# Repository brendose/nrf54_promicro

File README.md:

<h1 align="center">Welcome to Project: nrf54_promicro </br> (nRF54L1x Pro Micro inspired development board) </h1>
<div align="center">

<a href="#introduction">Introduction</a> &nbsp;&bull;&nbsp;
<a href="#directory">Directory</a> &nbsp;&bull;&nbsp;
<a href="#documentation">Documentation</a> &nbsp;&bull;&nbsp;
<a href="#notes">Notes</a>
</div>

# Introduction
The <b>nrf54_promicro</b> project revolutionizes nRF52840 based keyboard projects by utilizing the Nordic Semiconductors nRF54L10/L15 Bluetooth transceiver, achieving sub-100uA/MHz power draw!
<br>
<br>
We're challenging the status quo of limited wireless keyboard battery life with the nRF54L15/L10, achieving unprecedented power efficiency. Why? Because Bluetooth based keyboard designs require decent battery life.
The nRF52840 power draw limits the battery life of most keyboard based projects, however, moving to the nRF54 the power draw can be minimized to a under 100uA/MHz. This Pro Micro-inspired board, designed in KiCad 9, 
integrates optimized power circuitry such as; the use of a high efficiency switching power supply, carefully selected low quiescent current (Iq) load switch and meticulous RF antenna tuning, wasting no power and
offering a development platform for keyboards that redefines what it means to have "good battery life".

The board contains:

- A Nordic Semiconductors nRF54L10 / nRF54L15 (ARM Cortex M33 and RISC-V coprocessor)
- 2.45GHz Chip Antenna supporting Bluetooth LE
- Texas Instruments BQ24075 battery charger
- 2x 13 pin GPIO headers 
- USB-C connector, with bit-banged USB interface
- Charge Status indicator LED
- Bluetooth Status indicator LED

### Projects top-level directory

    .
    ├── bom                      # Bill of Materials
    ├── images                   # Images used on this GitHub page
    ├── libs                     # Local component library
    ├── plots                    # Assembly drawings of the design
    ├── schematics               # Schematics of the design      
    └── README.md

## Documentation

TBD

## Notes

This repository is not actively maintained, so if you spot any bugs, please <a href="hhttps://github.com/brendose/nrf54_promicro/issues/new">raise an issue</a> and I will try get to it.

This is not an officially supported Google product.

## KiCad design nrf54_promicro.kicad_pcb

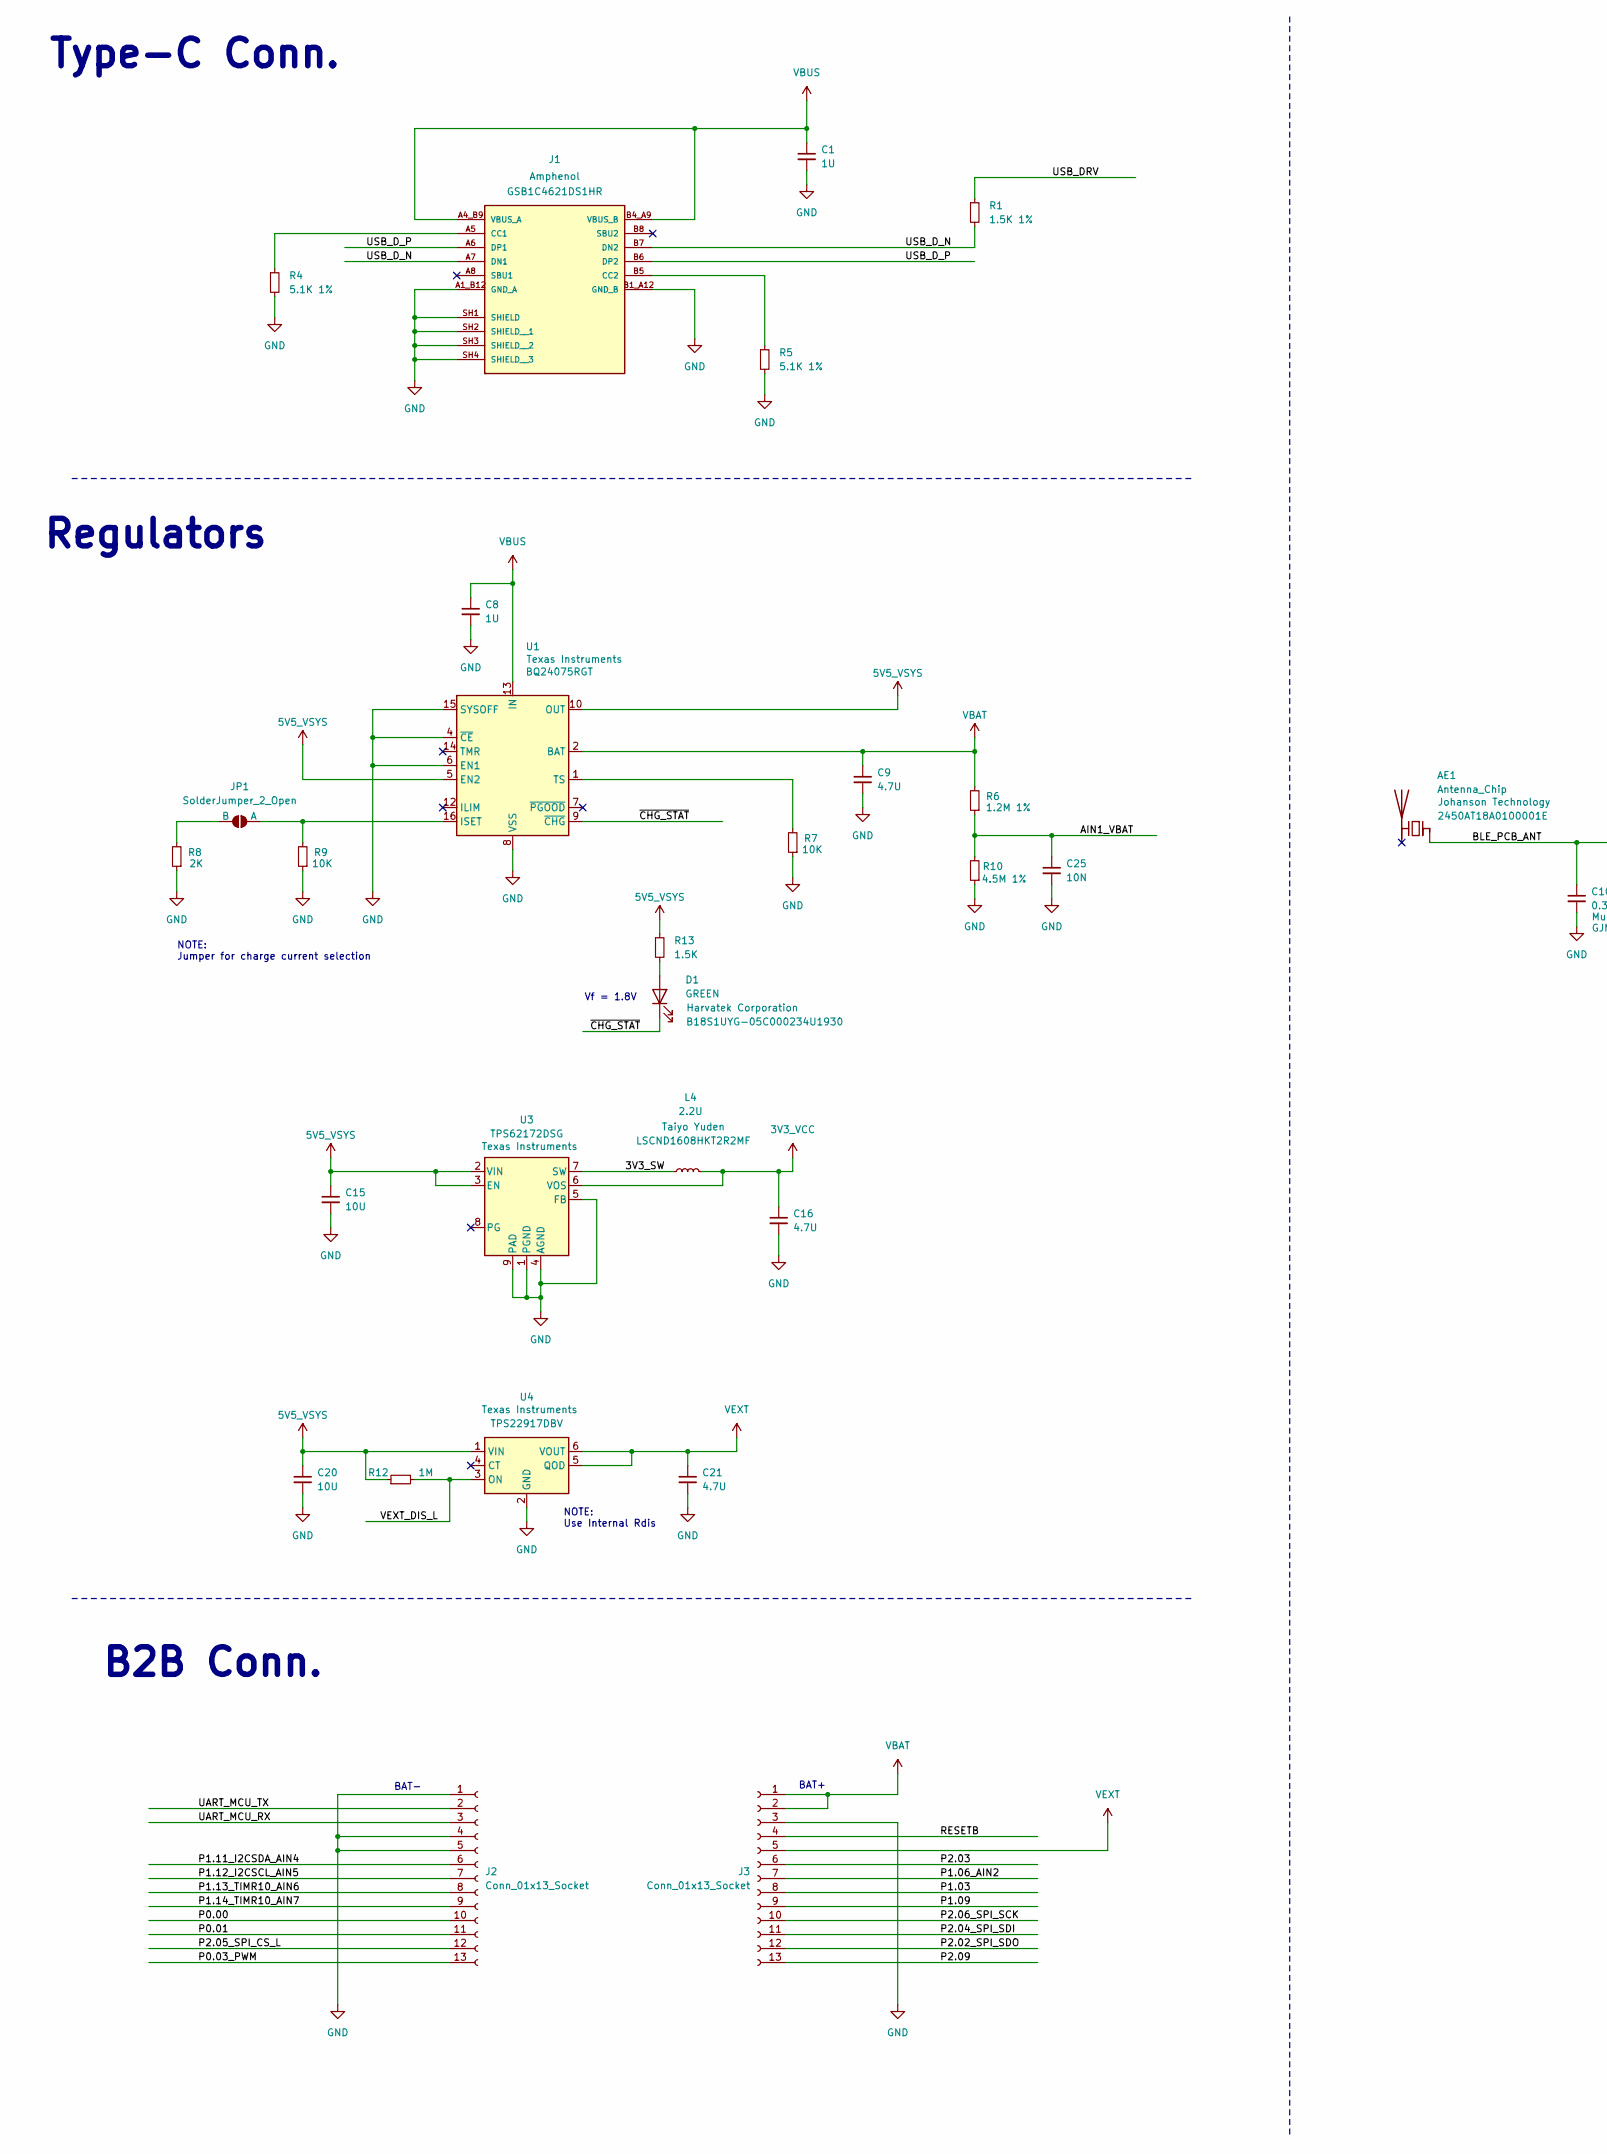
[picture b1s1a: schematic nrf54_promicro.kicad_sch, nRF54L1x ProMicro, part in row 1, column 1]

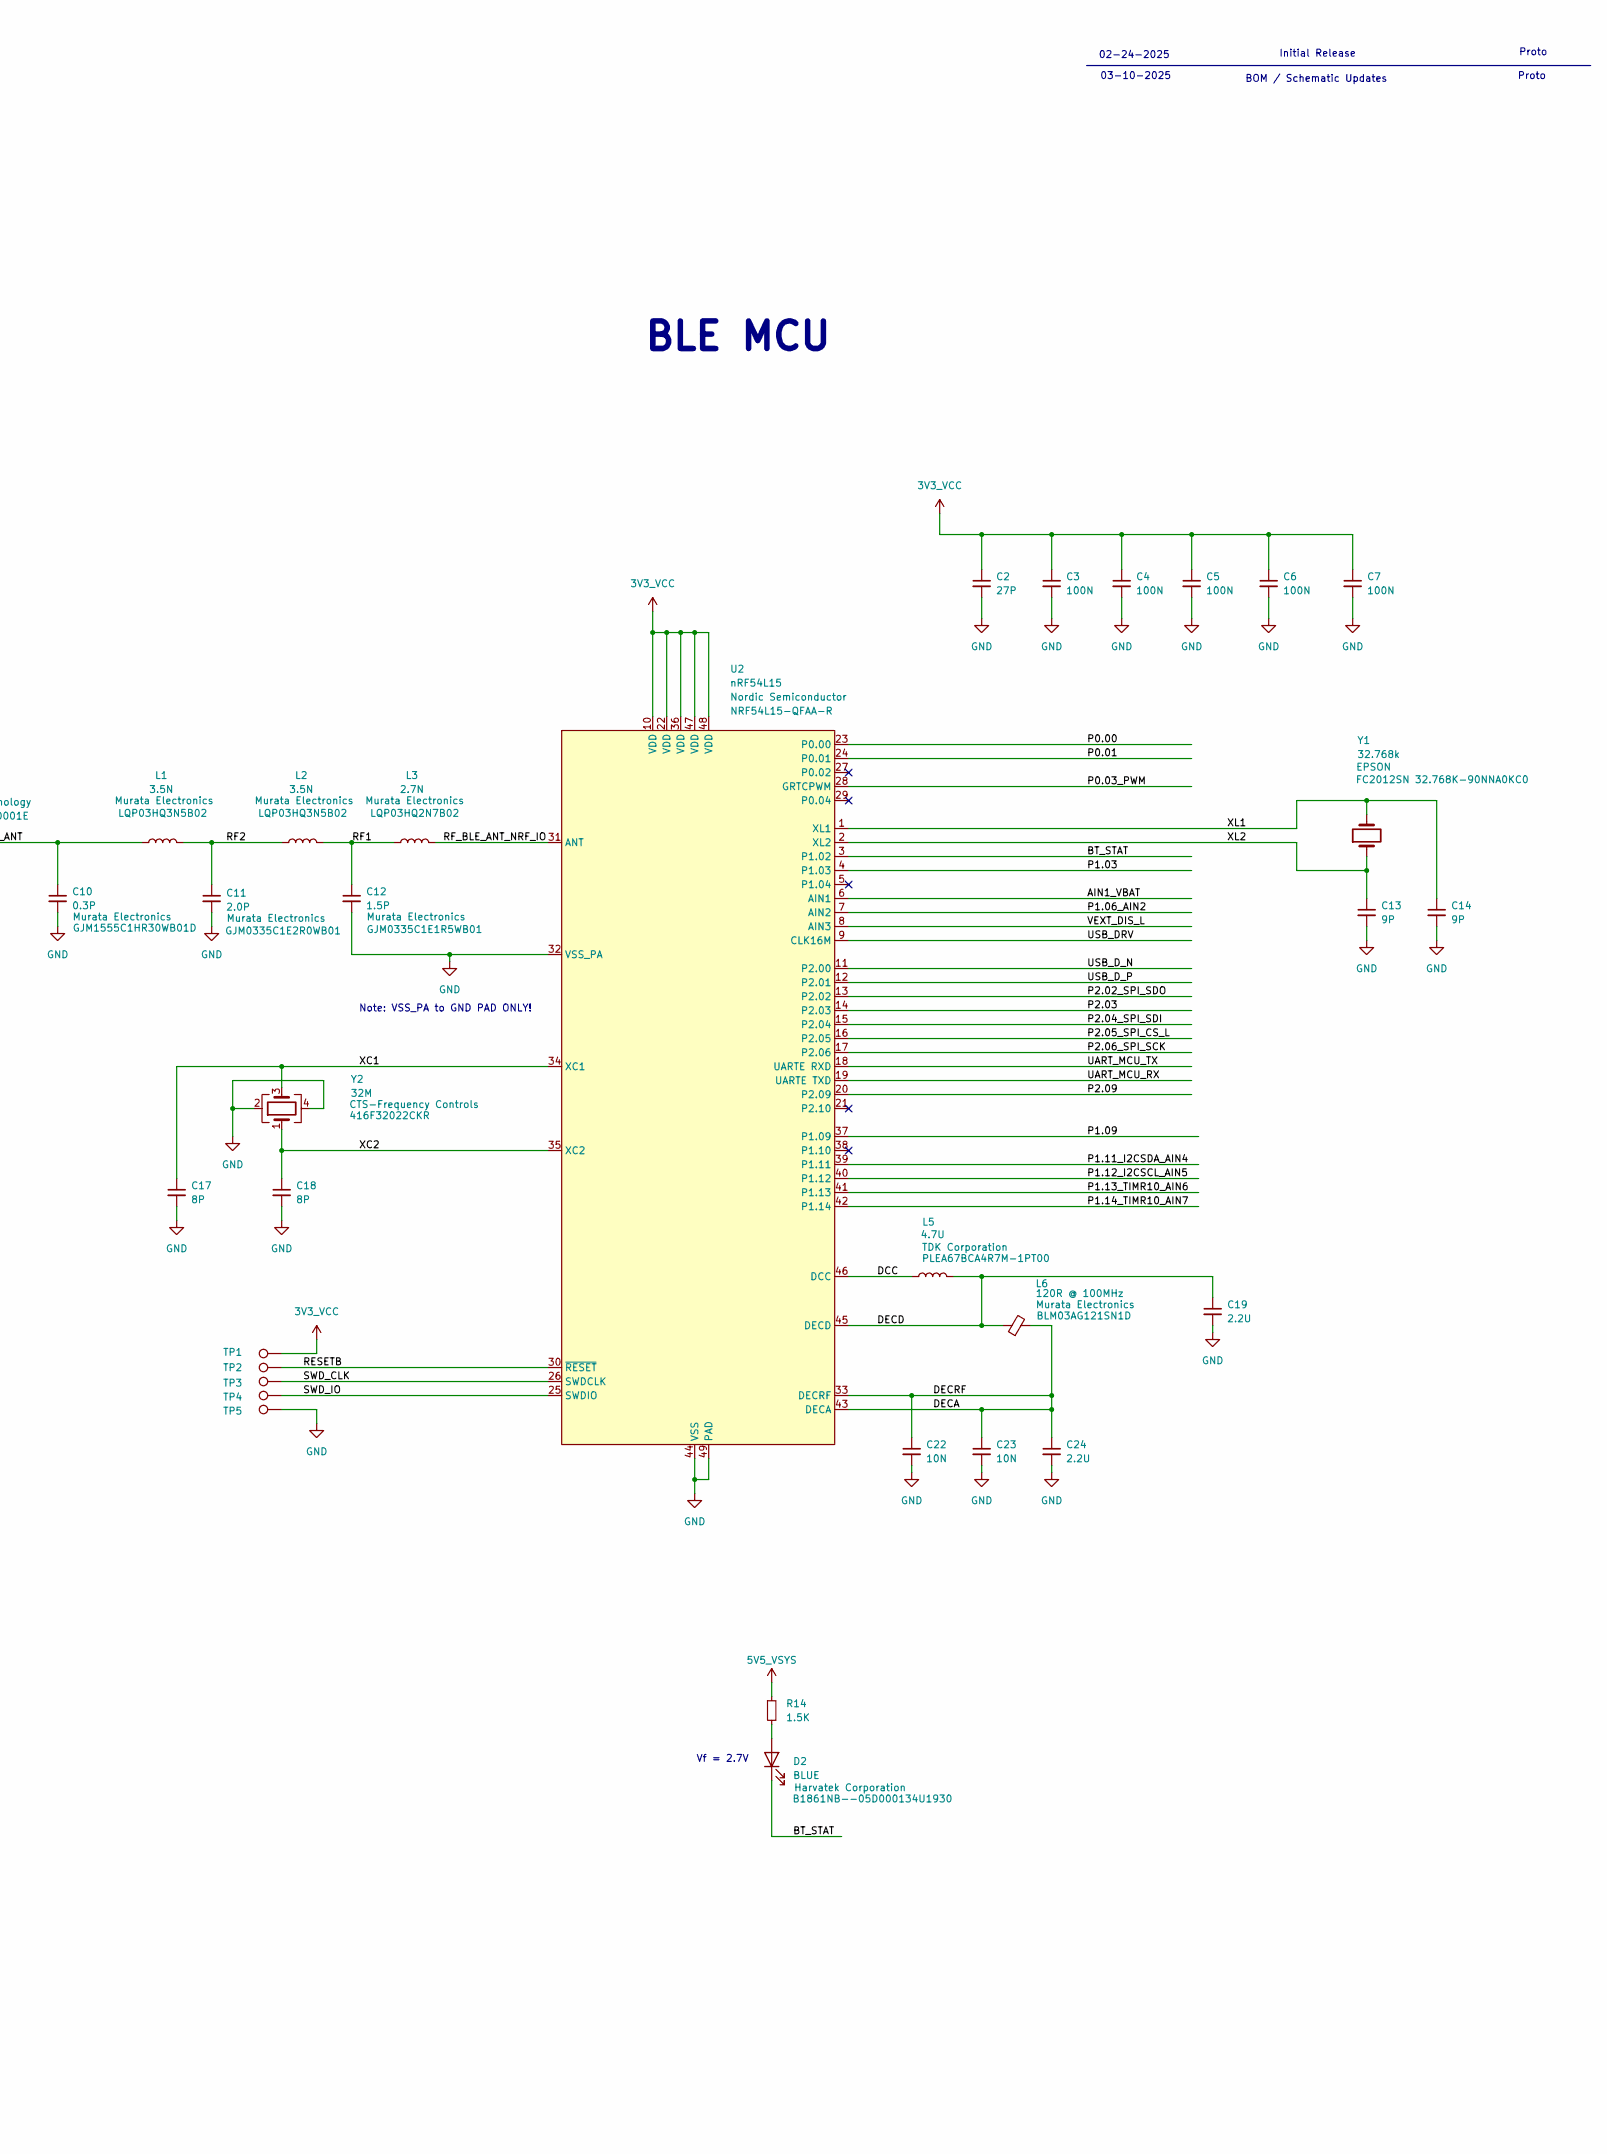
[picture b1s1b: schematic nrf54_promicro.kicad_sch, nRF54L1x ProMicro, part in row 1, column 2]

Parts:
AE1: Antenna_Chip; Johanson_2450AT18x100; MFG_PN 2450AT18A0100001E
C1, C8: 1U; C_0201_0603Metric
C2: 27P; C_0201_0603Metric
C3, C4, C5, C6, C7: 100N; C_0201_0603Metric
C9, C16, C21: 4.7U; C_0402_1005Metric
C10: 0.3P; C_0201_0603Metric; MFG_PN GJM1555C1HR30WB01D
C11: 2.0P; C_0201_0603Metric; MFG_PN GJM0335C1E2R0WB01
C12: 1.5P; C_0201_0603Metric; MFG_PN GJM0335C1E1R5WB01
C13, C14: 9P; C_0201_0603Metric
C15, C20: 10U; C_0402_1005Metric
C17, C18: 8P; C_0201_0603Metric
C19, C24: 2.2U; C_0402_1005Metric
C22, C23, C25: 10N; C_0201_0603Metric
D1: GREEN; LED_0402_1005Metric; MFG_PN B18S1UYG-05C000234U1930
D2: BLUE; LED_0402_1005Metric; MFG_PN B1861NB--05D000134U1930
J1: GSB1C4621DS1HR; AMPHENOL_GSB1C4621DS1HR; PARTREV AX1
J2, J3: Conn_01x13_Socket; PinHeader_1x13_P2.54mm_Vertical
JP1: SolderJumper_2_Open; SolderJumper-2_P1.3mm_Open_RoundedPad1.0x1.5mm
L1, L2: 3.5N; L_0201_0603Metric; MFG_PN LQP03HQ3N5B02
L3: 2.7N; L_0201_0603Metric; MFG_PN LQP03HQ2N7B02
L4: 2.2U; L_0603_1608Metric; MFG_PN LSCND1608HKT2R2MF
L5: 4.7U; L_0402_1005Metric; MFG_PN PLEA67BCA4R7M-1PT00
L6: 120R @ 100MHz; L_0201_0603Metric; MFG_PN BLM03AG121SN1D
R1: 1.5K 1%; R_0201_0603Metric
R4, R5: 5.1K 1%; R_0201_0603Metric
R6: 1.2M 1%; R_0201_0603Metric
R7, R9: 10K; R_0201_0603Metric
R8: 2K; R_0201_0603Metric
R10: 4.5M 1%; R_0201_0603Metric
R12: 1M; R_0201_0603Metric
R13, R14: 1.5K; R_0201_0603Metric
TP1, TP2, TP3, TP4, TP5: TestPoint; TestPoint_Pad_D1.0mm
U1: BQ24075RGT; VQFN-16-1EP_3x3mm_P0.5mm_EP1.6x1.6mm; MFG_PN BQ24075RGTR
U2: nRF54L15; QFN-48-1EP_6x6mm_P0.4mm_EP4.6x4.6mm; MFG_PN NRF54L15-QFAA-R
U3: TPS62172DSG; WSON-8-1EP_2x2mm_P0.5mm_EP0.9x1.6mm_ThermalVias; MFG_PN TPS62172DSGT
U4: TPS22917DBV; SOT-23-6; MFG_PN TPS22917DBVR
Y1: 32.768k; Crystal_SMD_2012-2Pin_2.0x1.2mm; MFG_PN FC2012SN 32.768K-90NNA0KC0
Y2: 32M; Oscillator_SMD_Abracon_ASCO-4Pin_1.6x1.2mm; MFG_PN 416F32022CKR

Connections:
3V3_VCC: C2.1, C3.1, C4.1, C5.1, C6.1, C7.1, C16.1, L4.2, TP1.1, U2.10 (VDD), U2.22 (VDD), U2.36 (VDD), U2.47 (VDD), U2.48 (VDD), U3.6 (VOS)
5V5_VSYS: C15.1, C20.1, R12.1, R13.1, R14.1, U1.5 (EN2), U1.10 (OUT), U1.11 (OUT), U3.2 (VIN), U3.3 (EN), U4.1 (VIN)
/3V3_SW: L4.1, U3.7 (SW)
/AIN1_VBAT: C25.1, R6.1, R10.2, U2.6 (AIN1)
/BLE_PCB_ANT: AE1.1 (FEED), C10.1, L1.1
/BT_STAT: D2.1 (K), U2.3 (P1.02)
/DCC: L5.1, U2.46 (DCC)
/DECA: C22.1, C23.1, C24.1, L6.2, U2.33 (DECRF), U2.43 (DECA)
/DECD: C19.1, L5.2, L6.1, U2.45 (DECD)
/P0.00: J2.10, U2.23 (P0.00)
/P0.01: J2.11, U2.24 (P0.01)
/P0.03_PWM: J2.13, U2.28 (GRTCPWM)
/P1.03: J3.8, U2.4 (P1.03)
/P1.06_AIN2: J3.7, U2.7 (AIN2)
/P1.09: J3.9, U2.37 (P1.09)
/P1.11_I2CSDA_AIN4: J2.6, U2.39 (P1.11)
/P1.12_I2CSCL_AIN5: J2.7, U2.40 (P1.12)
/P1.13_TIMR10_AIN6: J2.8, U2.41 (P1.13)
/P1.14_TIMR10_AIN7: J2.9, U2.42 (P1.14)
/P2.02_SPI_SDO: J3.12, U2.13 (P2.02)
/P2.03: J3.6, U2.14 (P2.03)
/P2.04_SPI_SDI: J3.11, U2.15 (P2.04)
/P2.05_SPI_CS_L: J2.12, U2.16 (P2.05)
/P2.06_SPI_SCK: J3.10, U2.17 (P2.06)
/P2.09: J3.13, U2.20 (P2.09)
/RESETB: J3.4, TP2.1, U2.30 (~RESET)
/RF1: C12.1, L2.2, L3.1
/RF2: C11.1, L1.2, L2.1
/RF_BLE_ANT_NRF_IO: L3.2, U2.31 (ANT)
/SWD_CLK: TP3.1, U2.26 (SWDCLK)
/SWD_IO: TP4.1, U2.25 (SWDIO)
/UART_MCU_RX: J2.3, U2.19 (UARTE TXD)
/UART_MCU_TX: J2.2, U2.18 (UARTE RXD)
/USB_DRV: R1.1, U2.9 (CLK16M)
/USB_D_N: J1.A7 (DN1), J1.B7 (DN2), R1.2, U2.11 (P2.00)
/USB_D_P: J1.A6 (DP1), J1.B6 (DP2), U2.12 (P2.01)
/VEXT_DIS_L: R12.2, U2.8 (AIN3), U4.3 (ON)
/XC1: C17.1, U2.34 (XC1), Y2.3
/XC2: C18.1, U2.35 (XC2), Y2.1
/XL1: C14.1, U2.1 (XL1), Y1.2
/XL2: C13.1, U2.2 (XL2), Y1.1
/~CHG_STAT: D1.1 (K), U1.9 (~CHG)
GND: C1.2, C2.2, C3.2, C4.2, C5.2, C6.2, C7.2, C8.2, C9.2, C10.2, C11.2, C12.2, C13.2, C14.2, C15.2, C16.2, C17.2, C18.2, C19.2, C20.2, C21.2, C22.2, C23.2, C24.2, C25.2, J1.A1_B12 (GND_A), J1.B1_A12 (GND_B), J1.SH1 (SHIELD), J1.SH2 (SHIELD__1), J1.SH3 (SHIELD__2), J1.SH4 (SHIELD__3), J2.1, J2.4, J2.5, J3.3, R4.2, R5.2, R7.1, R8.1, R9.1, R10.1, TP5.1, U1.4 (~CE), U1.6 (EN1), U1.8 (VSS), U1.15 (SYSOFF), U1.17 (VSS), U2.32 (VSS_PA), U2.44 (VSS), U2.49 (PAD), U3.1 (PGND), U3.4 (AGND), U3.5 (FB), U3.9 (PAD), U4.2 (GND), Y2.2, Y2.4
unnamed: D1.2 (A), R13.2
unnamed: D2.2 (A), R14.2
unnamed: J1.A5 (CC1), R4.1
unnamed: J1.B5 (CC2), R5.1
unnamed: JP1.1 (A), R9.2, U1.16 (ISET)
unnamed: JP1.2 (B), R8.2
unnamed: R7.2, U1.1 (TS)
VBAT: C9.1, J3.1, J3.2, R6.2, U1.2 (BAT), U1.3 (BAT)
VBUS: C1.1, C8.1, J1.A4_B9 (VBUS_A), J1.B4_A9 (VBUS_B), U1.13 (IN)
VEXT: C21.1, J3.5, U4.5 (QOD), U4.6 (VOUT)

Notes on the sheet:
Proto
NOTE: Jumper for charge current selection
03-10-2025
Note: VSS_PA to GND PAD ONLY!
BAT+
BOM / Schematic Updates
02-24-2025
Initial Release
BLE MCU
Type-C Conn.
NOTE: Use Internal Rdis
Vf = 2.7V
BAT-
Regulators
B2B Conn.
Vf = 1.8V

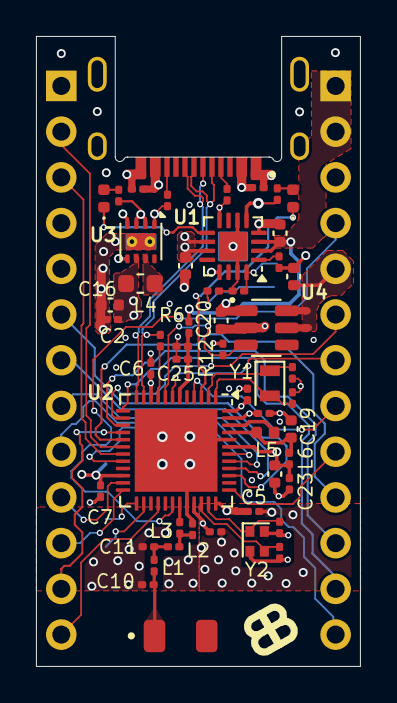
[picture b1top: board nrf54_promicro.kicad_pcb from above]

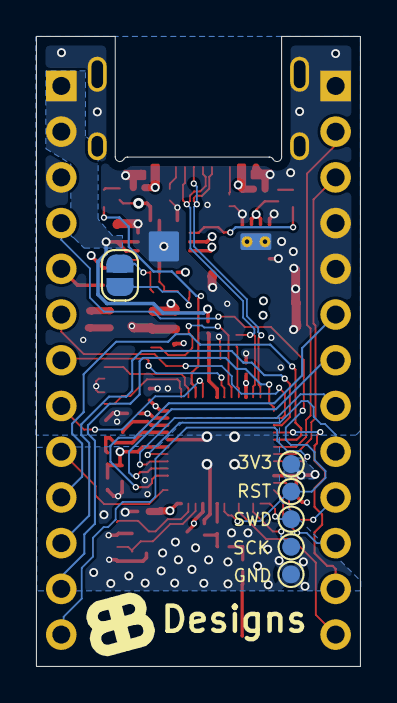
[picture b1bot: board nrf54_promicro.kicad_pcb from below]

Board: 4 copper layers, 18.0 x 35.0 mm, 60 parts (6 on the bottom side), 53 nets.

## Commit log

2025-02-24 Continued to improve layout. Updated README.md
2025-02-24 Improved Layout. Improved Silk/Fab.
2025-02-25 Swapped U4 for lower Iq load switch. Fixed DRCs. Fixed Layout.
2025-02-25 Updated REAMDME.md. Moved lib files. Generated some output documentation.
2025-02-25 Update README.md
    Updated Intro paragraph in README.md
2025-02-25 Update README.md
    Updated README.md formatting.
2025-03-02 BOM updates, schematic and layout updated due to BOM updated
2025-03-02 Assembly and SS layer updates, Image update.
2025-03-06 BOM Updates. Layout Updates.
2025-03-11 Moved USB_D_P/N to MCU Domain for increased bus BW. Improved RF layout. Improved PI. Changed IO for improved MCU escape.
2025-03-13 Fixed Assembly Layers.
2025-03-31 Modified layout - remove SPI LM. Removed GND shape around pins.
